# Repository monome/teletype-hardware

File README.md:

# teletype hardware

eurorack module by https://monome.org

created by brian crabtree (bcrabtree@monome.org)

all circuits in eagle. can be imported to kicad.

firmware: https://github.com/monome/teletype

## BOM

- components: see ods
- octopart: https://octopart.com/bom-tool/cjqXTx5c
- mechanical (screws and spacers)
  - mcmaster: 91780A023, 91772A077, 91772A073

## license

[cc-by-sa-3.0](https://creativecommons.org/licenses/by-sa/4.0/)

commerical use: send $10 per unit produced to tehn@nnnnnnnn.co via paypal

do not use the name "monome" or "teletype" in derivative works.

## warranty and support

we can provide neither

## thank you

everyone who helped this module live

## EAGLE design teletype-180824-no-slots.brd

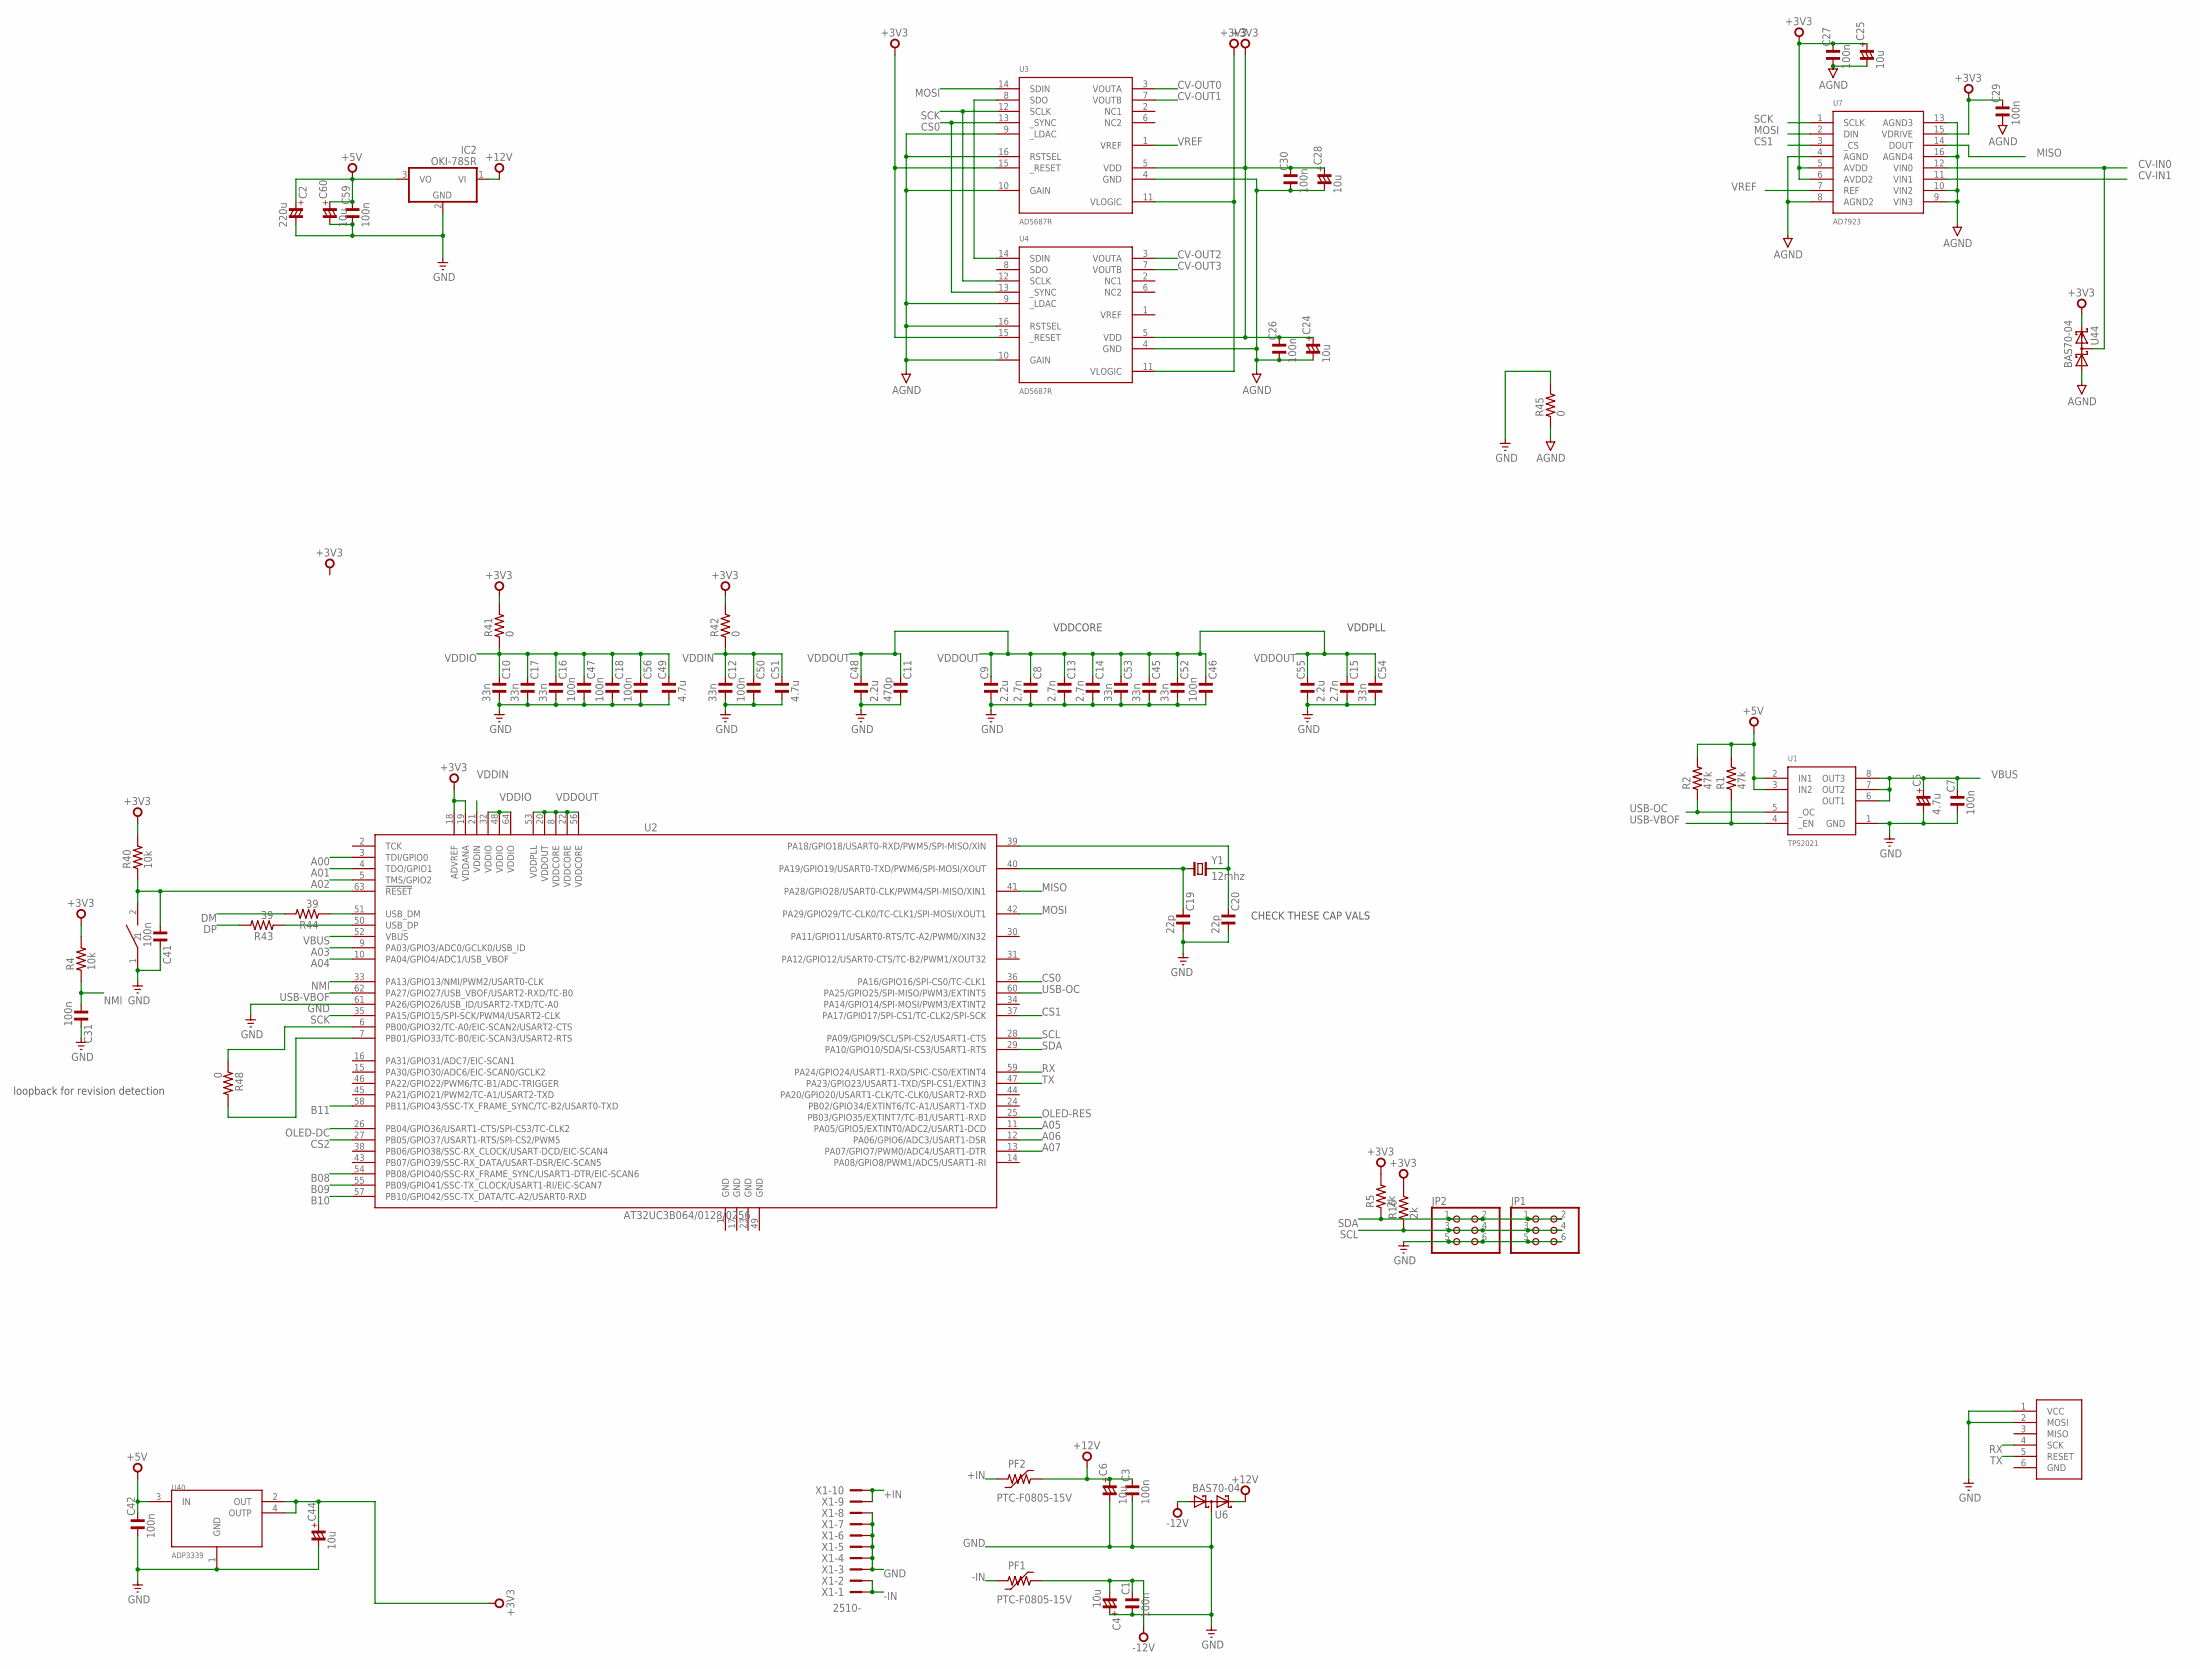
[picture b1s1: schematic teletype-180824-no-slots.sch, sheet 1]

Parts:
C1, C3, C7, C18, C26, C27, C29, C30, C31, C41, C42, C46, C47, C50, C56, C59: 100n; C0402
C2: 220u; C7343-43
C4, C6, C24, C25, C28, C44, C60: 10u; C1206/T
C5: 4.7u; C1206/T
C8, C13, C14, C15: 2.7n; C0402
C9, C48, C55: 2.2u; C0603
C10, C12, C16, C17, C45, C52, C53, C54: 33n; C0402
C11: 470p; C0402
C19, C20: 22p; C0402
C49, C51: 4.7u; C0603
IC2: OKI-78SR; TO220V
J40: ISP-ROW
JP1, JP2: PINHD-2X3; 2X03
PF1, PF2: PTC-F0805-15V; F1206
R1, R2: 47k; R0402
R4, R40: 10k; R0402
R5, R16: 2k; R0402
R41, R42, R48: 0; R0402
R43, R44: 39; R0402
R45: 0; R0603
SW40: PANASONIC-EVQ
U1: TPS2021; SO08
U2: AT32UC3B064/0128/0256; TQFP64-10X10
U3, U4: AD5687R; TSSOP16
U6, U44: BAS70-04; SOT23
U7: AD7923; TSSOP16
U40: ADP3339; SOT223
X1: 2510-; PAK100/2500-10
Y1: 12mhz; HC49UP

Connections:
+3V3: C24.+, C25.+, C26.2, C27.2, C28.+, C29.2, C30.2, C44.+, R4.2, R5.2, R16.2, R40.2, R41.2, R42.2, U2.18 (ADVREF), U2.19 (VDDANA), U3.5 (VDD), U3.11 (VLOGIC), U3.15 (_RESET), U4.5 (VDD), U4.11 (VLOGIC), U4.15 (_RESET), U7.5 (AVDD), U7.6 (AVDD2), U7.15 (VDRIVE), U40.2 (OUT), U40.4 (OUTP), U44.2 (C2); also elsewhere on the board
+5V: C2.+, C42.2, C59.2, C60.+, IC2.3 (VO), R1.2, R2.2, U1.2 (IN1), U1.3 (IN2), U40.3 (IN)
+12V: C3.2, C6.+, IC2.1 (VI), PF2.2, U6.2 (C2); also elsewhere on the board
+IN: PF2.1, X1.9, X1.10
-12V: C1.2, C4.-, PF1.2, U6.1 (A1); also elsewhere on the board
-IN: PF1.1, X1.1, X1.2
A00: U2.3 (TDI/GPIO0); also elsewhere on the board
A01: U2.4 (TDO/GPIO1); also elsewhere on the board
A02: U2.5 (TMS/GPIO2); also elsewhere on the board
A03: U2.9 (PA03/GPIO3/ADC0/GCLK0/USB_ID); also elsewhere on the board
A04: U2.10 (PA04/GPIO4/ADC1/USB_VBOF); also elsewhere on the board
A05: U2.11 (PA05/GPIO5/EXTINT0/ADC2/USART1-DCD); also elsewhere on the board
A06: U2.12 (PA06/GPIO6/ADC3/USART1-DSR); also elsewhere on the board
A07: U2.13 (PA07/GPIO7/PWM0/ADC4/USART1-DTR); also elsewhere on the board
AGND: C24.-, C25.-, C26.1, C27.1, C28.-, C29.1, C30.1, R45.1, U3.4 (GND), U3.9 (_LDAC), U3.10 (GAIN), U3.16 (RSTSEL), U4.4 (GND), U4.9 (_LDAC), U4.10 (GAIN), U4.16 (RSTSEL), U7.4 (AGND), U7.8 (AGND2), U7.9 (VIN3), U7.10 (VIN2), U7.13 (AGND3), U7.16 (AGND4), U44.1 (A1); also elsewhere on the board
B08: U2.54 (PB08/GPIO40/SSC-RX_FRAME_SYNC/USART1-DT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); also elsewhere on the board
B09: U2.55 (PB09/GPIO41/SSC-TX_CLOCK/USART1-RI/EIC-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); also elsewhere on the board
B10: U2.57 (PB10/GPIO42/SSC-TX_DATA/TC-A2/USART0-RXD); also elsewhere on the board
B11: U2.58 (PB11/GPIO43/SSC-TX_FRAME_SYNC/TC-B2/USA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); also elsewhere on the board
CS0: U2.36 (PA16/GPIO16/SPI-CS0/TC-CLK1), U3.13 (_SYNC), U4.13 (_SYNC)
CS1: U2.37 (PA17/GPIO17/SPI-CS1/TC-CLK2/SPI-SCK), U7.3 (_CS)
CS2: U2.27 (PB05/GPIO37/USART1-RTS/SPI-CS2/PWM5); also elsewhere on the board
CV-IN0: U7.12 (VIN0), U44.3 (C1A2); also elsewhere on the board
CV-IN1: U7.11 (VIN1); also elsewhere on the board
CV-OUT0: U3.3 (VOUTA); also elsewhere on the board
CV-OUT1: U3.7 (VOUTB); also elsewhere on the board
CV-OUT2: U4.3 (VOUTA); also elsewhere on the board
CV-OUT3: U4.7 (VOUTB); also elsewhere on the board
DM: R44.2; also elsewhere on the board
DP: R43.2; also elsewhere on the board
GND: C1.1, C2.-, C3.1, C4.+, C5.-, C6.-, C7.1, C8.1, C9.1, C10.1, C11.1, C12.1, C13.1, C14.1, C15.1, C16.1, C17.1, C18.1, C19.1, C20.1, C31.2, C41.2, C42.1, C44.-, C45.1, C46.1, C47.1, C48.1, C49.1, C50.1, C51.1, C52.1, C53.1, C54.1, C55.1, C56.1, C59.1, C60.-, IC2.2 (GND), J40.1 (VCC), J40.2 (MOSI), JP1.5, JP1.6, JP2.5, JP2.6, R45.2, SW40.1, U1.1 (GND), U2.1 (GND), U2.17 (GND), U2.23 (GND), U2.49 (GND), U2.61 (PA26/GPIO26/USB_ID/USART2-TXD/TC-A0), U6.3 (C1A2), U40.1 (GND), X1.3, X1.4, X1.5, X1.6, X1.7, X1.8; also elsewhere on the board
MISO: U2.41 (PA28/GPIO28/USART0-CLK/PWM4/SPI-MISO/XI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), U7.14 (DOUT)
MOSI: U2.42 (PA29/GPIO29/TC-CLK0/TC-CLK1/SPI-MOSI/XO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), U3.14 (SDIN), U7.2 (DIN); also elsewhere on the board
unnamed: R44.1, U2.51 (USB_DM)
unnamed: R43.1, U2.50 (USB_DP)
unnamed: U3.8 (SDO), U4.14 (SDIN)
unnamed: C20.2, U2.39 (PA18/GPIO18/USART0-RXD/PWM5/SPI-MISO/XIN), Y1.2
unnamed: R48.1, U2.6 (PB00/GPIO32/TC-A0/EIC-SCAN2/USART2-CTS)
unnamed: R48.2, U2.7 (PB01/GPIO33/TC-B0/EIC-SCAN3/USART2-RTS)
unnamed: C19.2, U2.40 (PA19/GPIO19/USART0-TXD/PWM6/SPI-MOSI/XO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), Y1.1
NMI: C31.1, R4.1, U2.33 (PA13/GPIO13/NMI/PWM2/USART0-CLK); also elsewhere on the board
OLED-DC: U2.26 (PB04/GPIO36/USART1-CTS/SPI-CS3/TC-CLK2); also elsewhere on the board
OLED-RES: U2.25 (PB03/GPIO35/EXTINT7/TC-B1/USART1-RXD); also elsewhere on the board
RESET: C41.1, R40.1, SW40.2, U2.63 (!RESET)
RX: J40.4 (SCK), U2.59 (PA24/GPIO24/USART1-RXD/SPIC-CS0/EXTINT4)
SCK: U2.35 (PA15/GPIO15/SPI-SCK/PWM4/USART2-CLK), U3.12 (SCLK), U4.12 (SCLK), U7.1 (SCLK); also elsewhere on the board
SCL: JP1.3, JP1.4, JP2.3, JP2.4, R16.1, U2.28 (PA09/GPIO9/SCL/SPI-CS2/USART1-CTS)
SDA: JP1.1, JP1.2, JP2.1, JP2.2, R5.1, U2.29 (PA10/GPIO10/SDA/SI-CS3/USART1-RTS)
TX: J40.5 (RESET), U2.47 (PA23/GPIO23/USART1-TXD/SPI-CS1/EXTIN3)
USB-OC: R2.1, U1.5 (_OC), U2.60 (PA25/GPIO25/SPI-MISO/PWM3/EXTINT5)
USB-VBOF: R1.1, U1.4 (_EN), U2.62 (PA27/GPIO27/USB_VBOF/USART2-RXD/TC-B0)
VBUS: C5.+, C7.2, U1.6 (OUT1), U1.7 (OUT2), U1.8 (OUT3), U2.52 (VBUS); also elsewhere on the board
VDDIN: C12.2, C50.2, C51.2, R42.1, U2.21 (VDDIN)
VDDIO: C10.2, C16.2, C17.2, C18.2, C47.2, C49.2, C56.2, R41.1, U2.32 (VDDIO), U2.48 (VDDIO), U2.64 (VDDIO)
VDDOUT: C8.2, C9.2, C11.2, C13.2, C14.2, C15.2, C45.2, C46.2, C48.2, C52.2, C53.2, C54.2, C55.2, U2.8 (VDDCORE), U2.20 (VDDOUT), U2.22 (VDDCORE), U2.53 (VDDPLL), U2.56 (VDDCORE)
VREF: U3.1 (VREF), U7.7 (REF)

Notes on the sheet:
CHECK THESE CAP VALS
VDDCORE
VDDPLL
loopback for revision detection

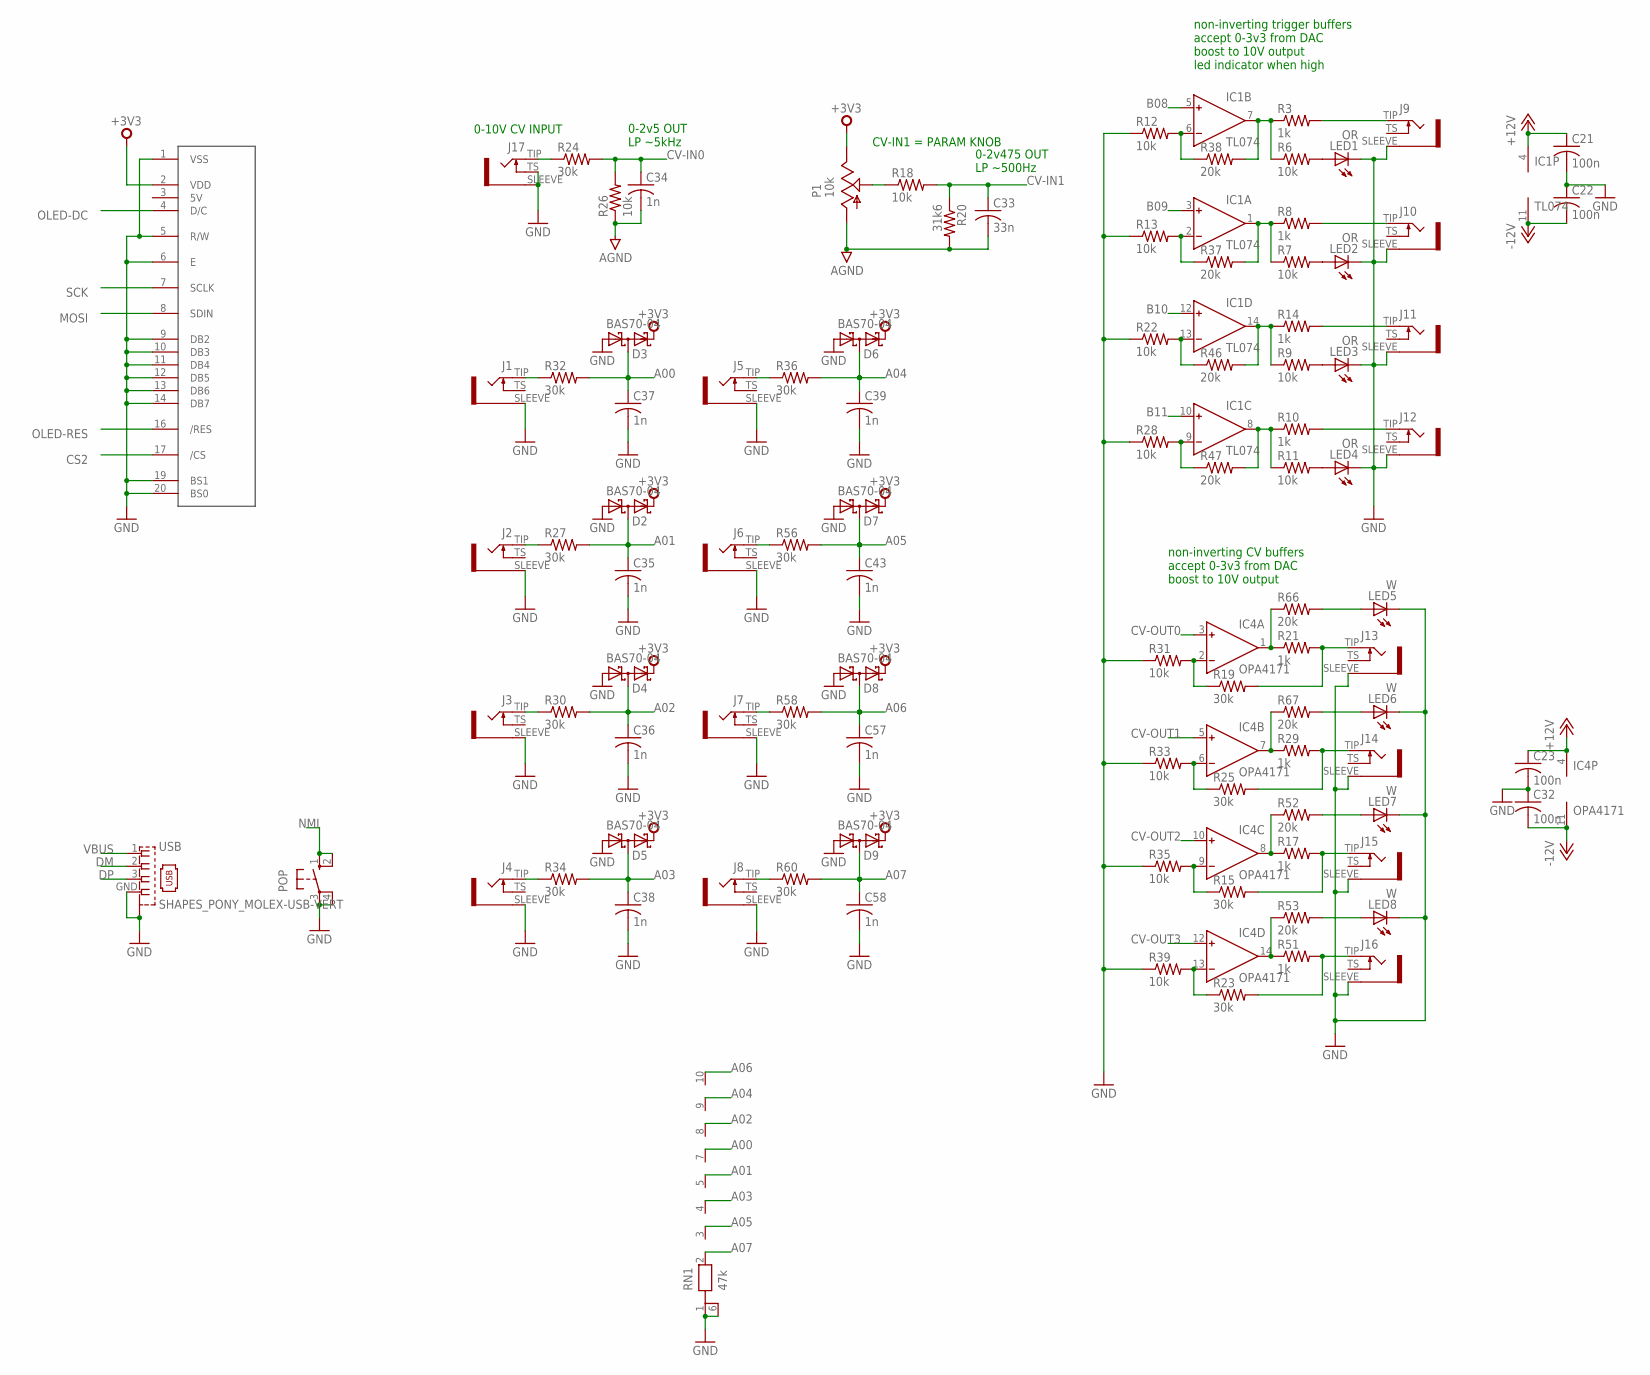
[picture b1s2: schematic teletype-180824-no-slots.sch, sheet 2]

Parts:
C21, C22, C23, C32: 100n; C0402
C33: 33n; C0402
C34, C35, C36, C37, C38, C39, C43, C57, C58: 1n; C0402
D2, D3, D4, D5, D6, D7, D8, D9: BAS70-04; SOT23
IC1: TL074; SO14
IC4: OPA4171; SO14; MPN AD8644ARZ
J1, J2, J3, J4, J5, J6, J7, J8, J9, J10, J11, J12, J13, J14, J15, J16, J17: WQP-PJ301M-12_JACK
LED1, LED2, LED3, LED4: OR; CHIP-LED0805
LED5, LED6, LED7, LED8: W; CHIP-LED0805
P1: 10k; ALPS_POT_VERTICAL
POP: SWITCH-OMRON_10-XX; SWITCH-OMRON_B3F-10XX
R3, R8, R10, R14, R17, R21, R29, R51: 1k; R0402
R6, R7, R9, R11, R12, R13, R18, R22, R26, R28, R31, R33, R35, R39: 10k; R0402
R15, R19, R23, R24, R25, R27, R30, R32, R34, R36, R56, R58, R60: 30k; R0402
R20: 31k6; R0402
R37, R38, R46, R47, R52, R53, R66, R67: 20k; R0402
RN1: 47k; MNR35
U$1: OLED128X64; OLED-ALEPH
USB: SHAPES_PONY_MOLEX-USB-VERT; SHAPES_PONY_MOLEX-USB

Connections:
+3V3: D2.2 (C2), D3.2 (C2), D4.2 (C2), D5.2 (C2), D6.2 (C2), D7.2 (C2), D8.2 (C2), D9.2 (C2), P1.P$1 (E), U$1.2 (VDD); also elsewhere on the board
+12V: C21.1, C23.1, IC1.4 (V+), IC4.4 (V+); also elsewhere on the board
-12V: C22.2, C32.2, IC1.11 (V-), IC4.11 (V-); also elsewhere on the board
A00: C37.1, D3.3 (C1A2), R32.2, RN1.7 (6); also elsewhere on the board
A01: C35.1, D2.3 (C1A2), R27.2, RN1.5; also elsewhere on the board
A02: C36.1, D4.3 (C1A2), R30.2, RN1.8 (7); also elsewhere on the board
A03: C38.1, D5.3 (C1A2), R34.2, RN1.4; also elsewhere on the board
A04: C39.1, D6.3 (C1A2), R36.2, RN1.9 (8); also elsewhere on the board
A05: C43.1, D7.3 (C1A2), R56.2, RN1.3; also elsewhere on the board
A06: C57.1, D8.3 (C1A2), R58.2, RN1.10 (9); also elsewhere on the board
A07: C58.1, D9.3 (C1A2), R60.2, RN1.2; also elsewhere on the board
AGND: C33.2, C34.2, P1.P$3 (A), R20.2, R26.1; also elsewhere on the board
B08: IC1.5 (IN+); also elsewhere on the board
B09: IC1.3 (IN+); also elsewhere on the board
B10: IC1.12 (IN+); also elsewhere on the board
B11: IC1.10 (IN+); also elsewhere on the board
CS2: U$1.17 (/CS); also elsewhere on the board
CV-IN0: C34.1, R24.2, R26.2; also elsewhere on the board
CV-IN1: C33.1, R18.2, R20.1; also elsewhere on the board
CV-OUT0: IC4.3 (IN+); also elsewhere on the board
CV-OUT1: IC4.5 (IN+); also elsewhere on the board
CV-OUT2: IC4.10 (IN+); also elsewhere on the board
CV-OUT3: IC4.12 (IN+); also elsewhere on the board
DM: USB.2; also elsewhere on the board
DP: USB.3; also elsewhere on the board
GND: C21.2, C22.1, C23.2, C32.1, C35.2, C36.2, C37.2, C38.2, C39.2, C43.2, C57.2, C58.2, D2.1 (A1), D3.1 (A1), D4.1 (A1), D5.1 (A1), D6.1 (A1), D7.1 (A1), D8.1 (A1), D9.1 (A1), J1.SLEEVE, J2.SLEEVE, J3.SLEEVE, J4.SLEEVE, J5.SLEEVE, J6.SLEEVE, J7.SLEEVE, J8.SLEEVE, J9.SLEEVE, J10.SLEEVE, J11.SLEEVE, J12.SLEEVE, J13.SLEEVE, J14.SLEEVE, J15.SLEEVE, J16.SLEEVE, J17.SLEEVE, J17.TS, LED1.C, LED2.C, LED3.C, LED4.C, LED5.C, LED6.C, LED7.C, LED8.C, POP.3, POP.4 (P1), R12.1, R13.1, R22.1, R28.1, R31.1, R33.1, R35.1, R39.1, RN1.1, RN1.6 (10), U$1.1 (VSS), U$1.5 (R/W), U$1.6 (E), U$1.9 (DB2), U$1.10 (DB3), U$1.11 (DB4), U$1.12 (DB5), U$1.13 (DB6), U$1.14 (DB7), U$1.19 (BS1), U$1.20 (BS0), USB.GND, USB.M1 (S1), USB.M2 (S1), USB.M4 (S1); also elsewhere on the board
MOSI: U$1.8 (SDIN); also elsewhere on the board
unnamed: IC1.7 (OUT), R3.1, R6.1, R38.2
unnamed: IC1.1 (OUT), R7.1, R8.1, R37.2
unnamed: IC1.14 (OUT), R9.1, R14.1, R46.2
unnamed: IC1.8 (OUT), R10.1, R11.1, R47.2
unnamed: J9.TIP, R3.2
unnamed: J10.TIP, R8.2
unnamed: J11.TIP, R14.2
unnamed: J12.TIP, R10.2
unnamed: P1.P$2 (S), R18.1
unnamed: IC4.1 (OUT), R21.1, R66.1
unnamed: IC4.7 (OUT), R29.1, R67.1
unnamed: LED5.A, R66.2
unnamed: J15.TIP, R15.2, R17.2
unnamed: J16.TIP, R23.2, R51.2
unnamed: IC4.8 (OUT), R17.1, R52.1
unnamed: LED6.A, R67.2
unnamed: IC4.14 (OUT), R51.1, R53.1
unnamed: LED7.A, R52.2
unnamed: LED8.A, R53.2
unnamed: J13.TIP, R19.2, R21.2
unnamed: J17.TIP, R24.1
unnamed: J14.TIP, R25.2, R29.2
unnamed: J2.TIP, R27.1
unnamed: J3.TIP, R30.1
unnamed: J4.TIP, R34.1
unnamed: J1.TIP, R32.1
unnamed: J5.TIP, R36.1
unnamed: J6.TIP, R56.1
unnamed: J7.TIP, R58.1
unnamed: J8.TIP, R60.1
unnamed: LED1.A, R6.2
unnamed: LED2.A, R7.2
unnamed: LED3.A, R9.2
unnamed: LED4.A, R11.2
NMI: POP.1 (S), POP.2 (S1); also elsewhere on the board
OLED-DC: U$1.4 (D/C); also elsewhere on the board
OLED-RES: U$1.16 (/RES); also elsewhere on the board
RG1: IC1.6 (IN-), R12.2, R38.1
RG2: IC1.2 (IN-), R13.2, R37.1
RG3: IC1.13 (IN-), R22.2, R46.1
RG4: IC1.9 (IN-), R28.2, R47.1
RG5: IC4.2 (IN-), R19.1, R31.2
RG6: IC4.6 (IN-), R25.1, R33.2
RG7: IC4.9 (IN-), R15.1, R35.2
RG8: IC4.13 (IN-), R23.1, R39.2
SCK: U$1.7 (SCLK); also elsewhere on the board
VBUS: USB.1; also elsewhere on the board

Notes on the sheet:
non-inverting CV buffers accept 0-3v3 from DAC boost to 10V output
non-inverting trigger buffers accept 0-3v3 from DAC boost to 10V output led indicator when high
CV-IN1 = PARAM KNOB
0-10V CV INPUT
0-2v5 OUT LP ~5kHz
0-2v475 OUT LP ~500Hz

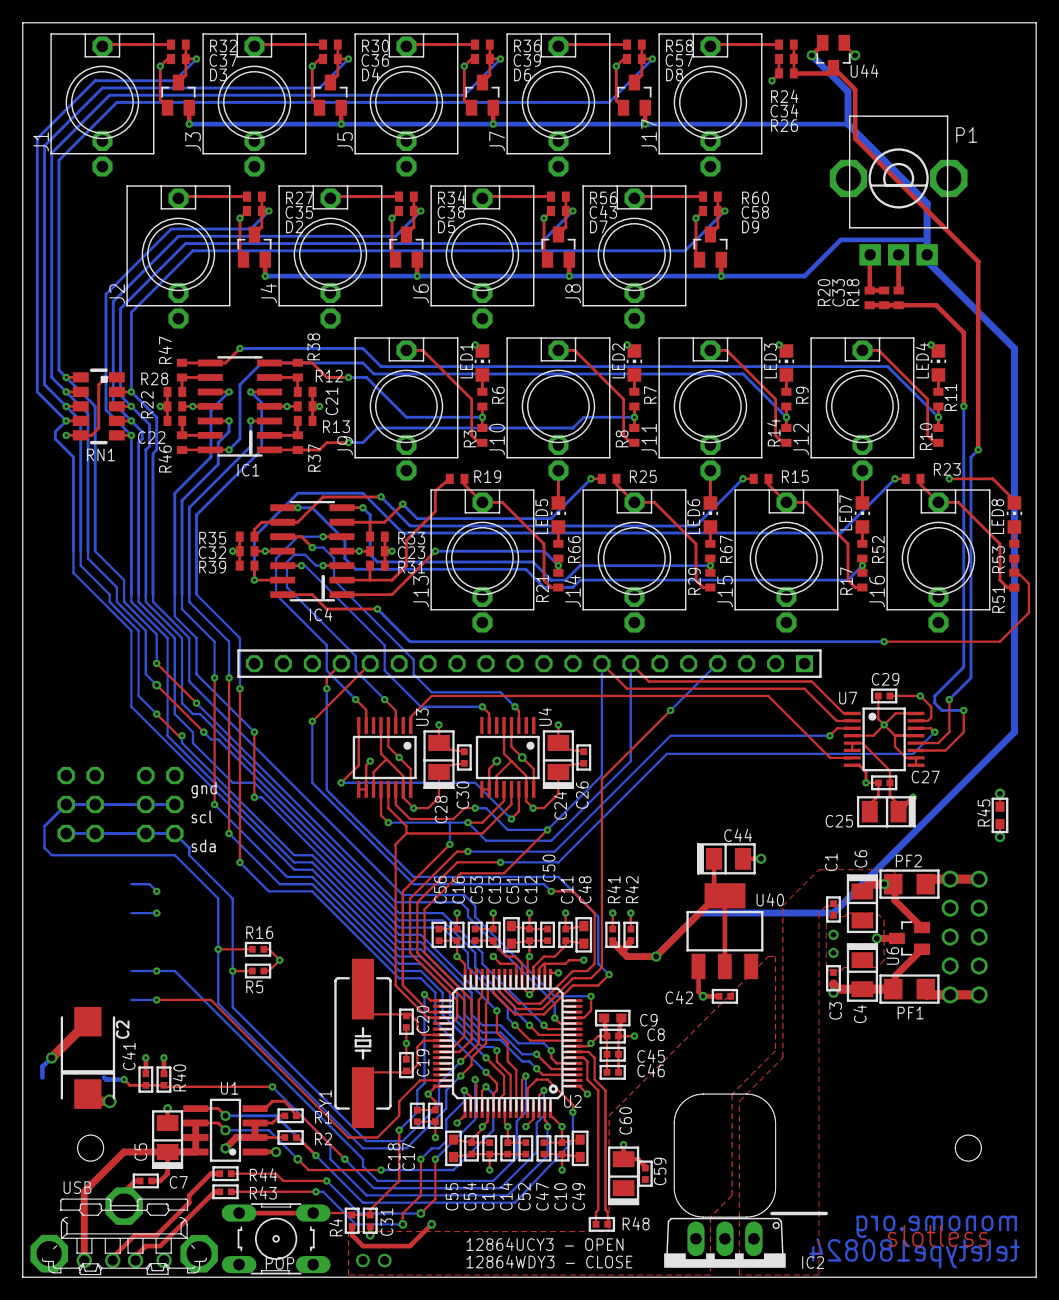
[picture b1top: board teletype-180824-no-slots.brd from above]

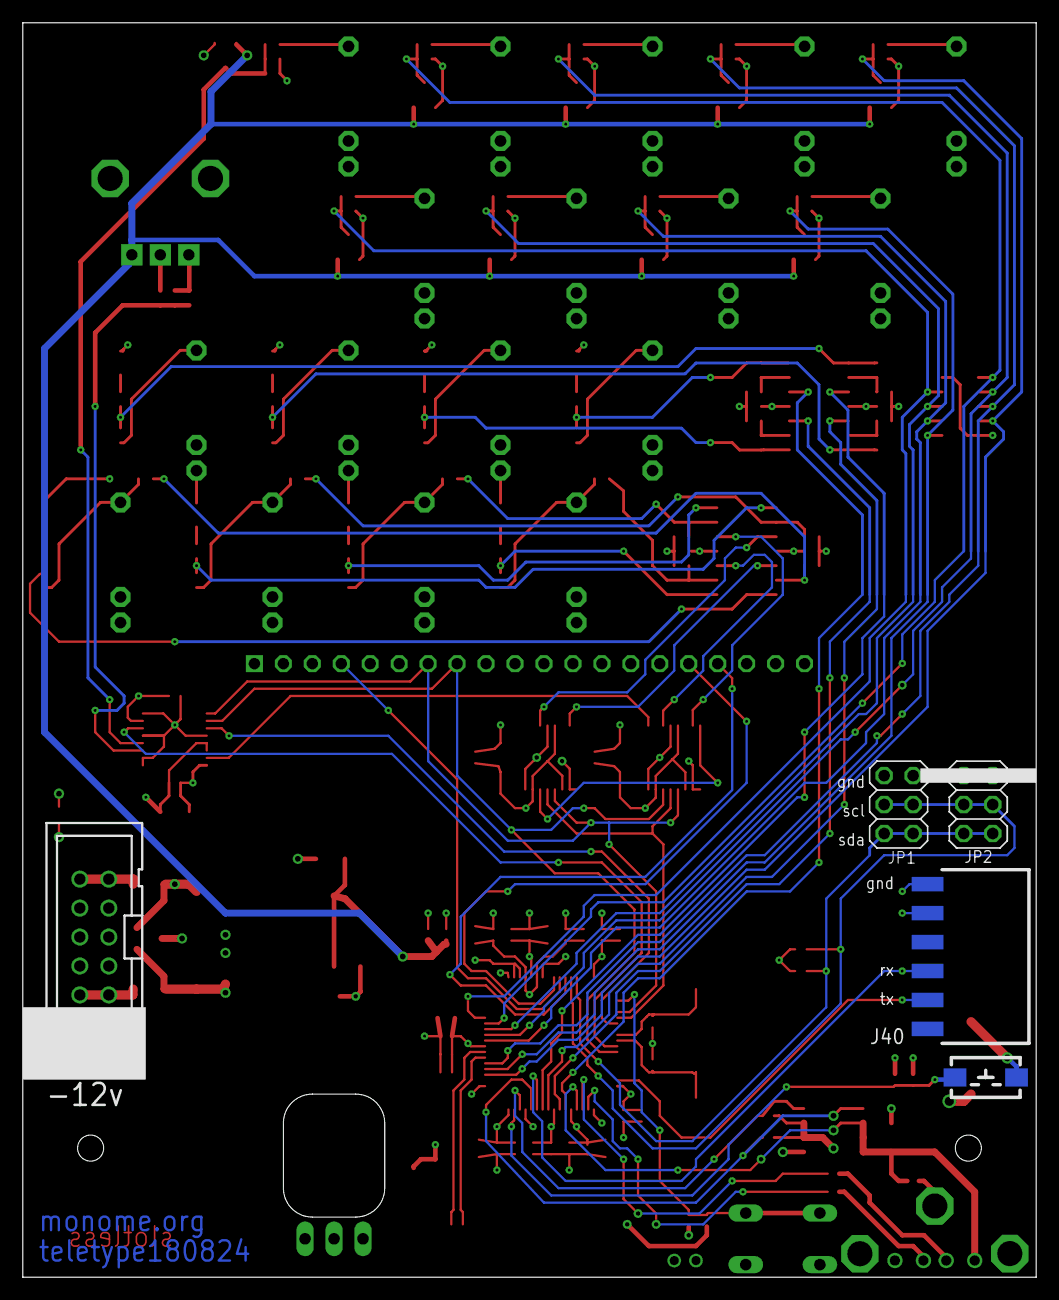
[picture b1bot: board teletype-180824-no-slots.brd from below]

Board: 4 copper layers, 88.9 x 110.0 mm, 172 parts (5 on the bottom side), 98 nets.

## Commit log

2019-11-20 initial
2019-11-20 bom link
2019-11-26 screencover
2019-11-26 mcmaster
2020-06-16 An alternative version with all slots from the board (this may be easier for some fab houses to manufacture)
2020-06-20 An alternative version with all slots from the board (this may be easier for some fab houses to manufacture) (#1)
2026-05-24 photo, ods bom
2026-05-24 readme

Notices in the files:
parts and their libraries:
atmel-avr32-michel-rev1: Copyright (C) 2010 Michel Catudal mcatudal@comcast.net
polyswitch: Copyright (C) 2008, Bob Starr
